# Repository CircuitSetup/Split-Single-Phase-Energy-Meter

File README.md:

# CircuitSetup Split Single Phase Energy Meter

The CircuitSetup ATM90E32 Split Single Phase Energy Meter can monitor the energy usage in your entire home in real time. It can easily be hooked up to an ESP8266 or ESP32 to wirelessly transmit energy usage data into a program like EmonCMS or ESPHome/Home Assistant. It can also be used to monitor solar power generation to keep track of how much power you are making.

#### With the Split Single Phase Energy Meter you can:

*   **Save Money!**
    *   See exactly how much money you're spending on energy in real time
    *   Find appliances that are using too much electricity
    *   Calculate energy usage for a single room to divide an energy bill fairly among roommates
*   **View & Gather Energy Data**
    *   View the energy usage of your entire home
    *   Track solar power generation (two units required)
    *   Calculate how much it costs to charge your electric vehicle
    *   Remote energy monitoring for vacation or rental properties
    *   Review and graph historical energy data
*   **Be Informed!**
    *   Independent of your power utility's meter
    *   Set up alerts for over or under usage
    *   Prevent surprises on energy bills
    *   View usage data in the EmonCMS Android or iOS apps
    *   Automate notifications with your home automation system like "send my phone a message when the dryer is done", or even "if I leave the house, and the oven is on, send me an alert" (programming required)
*   **Spend less on energy monitoring hardware!**
    *   Affordable but very accurate
    *   Save hundreds over popular monitoring systems

The Energy Meter kit available on CrowdSupply:

## Contents

<!-- toc -->
- [Features](#features)
- [Software Setup](#software-setup)
- [Hardware Setup](#hardware-setup)
- [Calibration](#calibration)
- [Troubleshooting](#troubleshooting)
<!-- tocstop -->

## Features:

* **IC: MicroChip ATM90E32**
* **Connectivity**
     * SPI Interface to connect to any Arduino compatible MCU
     * Two IRQ interrupts, and one Warning output
     * Energy pulse output (pulses correspond to four LEDs)
     * Zero crossing output
* **Real Time Data Sampling**
     * Two current channels - up to 200A per channel
     * One voltage channel (expandable to two)
     * Measurement Error: 1%
     * Dynamic Range: 6000:1
     * Gain Selection: Up to 4x
     * Voltage Reference Drift Typical (ppm/°C): 6
     * ADC Resolution (bits): 16
* **Calculates**
     * Active Power
     * Reactive Power
     * Apparent Power
     * Power Factor
     * Frequency
     * Temperature
* **Other Features**
     * Can use more than one at a time to measure as many circuits as you want, including solar power generation
     * Uses standard current transformer clamps to sample current
     * Includes built-in 500mA 3v3 buck converter to power MCU board 
     * Compact size at only 40 mm x 50 mm

## What you'll need:

* Current Transformers for wire:
   * **13mm and less**, the [SCT-013-000 100A/50mA](https://circuitsetup.us/index.php/product/100a-50ma-current-transformer-yhdc-sct-013/) has a 13mm opening for wire.
   * **13.5mm - 16mm - 4/0 AWG** (usually aluminum, 200A service) not thicker than 16mm with insulation, we recommend the [YHDC SCT-016 120A/40mA](https://circuitsetup.us/index.php/product/120a-40ma-current-transformer-yhdc-sct-016-with-3-5mm-jack-16mm-opening/). The ones available on CircuitSetup.us, and included with the energy meter kit have 3.5mm plugs. 

   * **Greater than 16mm**, the [Magnelab SCT-0750-100](https://amzn.to/2IF8xnY) (must sever burden resistor connection on the back of the board since they have a built in burden resistor). These have wire leads and will need an adapter or screw connectors soldered to the energy meter board.

   * Other CTs can also be used as long as they're rated for the amount of power that you are wanting to measure and have a current output no more than 720mA. For safety, they MUST have a built in Zener diode or burden resistor. 
* AC Transformer: [Jameco Reliapro 9v](https://amzn.to/2XcWJjI)
* An [ESP32](https://amzn.to/2pCtTtz), ESP8266, LoRa, or anything else that has an SPI interface.
* Jumper wires with Dupont connectors, or perf board to connect the two boards. The energy meter kit comes with a PCB adapter for an ESP32.
* The software located here to load onto your controller
* [EmonCMS](https://emoncms.org/site/home), ThingSpeak, InfluxDB/Grafana, or similar

## Software Setup

If you purchased an energy meter kit EmonESP is pre-loaded onto the included ESP32. You can skip this section and go to [Setting up EmonCMS](#setting-up-emoncms)

1.  Clone this repository in GitHub desktop or [download all the files and extract them to a folder](https://github.com/CircuitSetup/Split-Single-Phase-Energy-Meter/archive/master.zip)
2.  Place the ATM90E32 folder in your Arduino libraries folder. This is usually under Documents > Arduino > libraries
3.  We highly recommend using [EmonCMS.](https://emoncms.org/site/home) - EmonESP helps to connect and send data directly to EmonCMS
4.  Open **EmonESP > src > src.ino** - you will see several files open, but you'll only need to worry about src.ino
5.  Make sure the **CS_pin** is set to the pin that you are using on your controller board - the defaults are listed in src.ino and in the [hardware section here.](#hardware-setup)
6.  Upload the src.ino to your ESP (If you get any errors at this point, like a missing library, check the [Troubleshooting section on the EmonESP readme.](Software/EmonESP#troubleshooting-upload))
   If you are using an ESP32, [make sure you are using the latest software from the Espressif repository.](https://github.com/espressif/arduino-esp32)
7.  Upload files to the ESP in the data directory via SPIFFS - [see details on how to do this here](https://github.com/CircuitSetup/Split-Single-Phase-Energy-Meter/tree/master/Software/EmonESP#2-install-esp-filesystem-file-uploader)
8.  Follow the directions to configure the Access Point in the [EmonESP directions](/Software/EmonESP#first-setup)

### Setting up EmonCMS 

There are a few options for doing this:
- You can use the [EmonCMS.org service](https://emoncms.org/site/home), which costs roughly $15 a year with the data that we send from the energy meter (you don't _have_ to send all of the data)
- [Install on a computer within your network](https://github.com/emoncms/emoncms). To do this, you will need to have [apache/php/mysql installed](https://www.znetlive.com/blog/how-to-install-apache-php-and-mysql-on-windows-10-machine/)) [This can also be done with a Raspberry Pi.](https://github.com/emoncms/emoncms/blob/master/docs/RaspberryPi/readme.md)
- [Install on a remote web server](https://github.com/emoncms/emoncms). There are some very cheap ways this can be done if you're familiar with setting up web applications.

If you install EmonCMS on a remote web server, or if your home network has a public facing port, this will make it possible to see data on the EmonCMS app ([Android](https://play.google.com/store/apps/details?id=org.emoncms.myapps) or [iOS](https://itunes.apple.com/us/app/emoncms/id1169483587?ls=1&mt=8)) when your phone is outside of your network.

For all but the EmonCMS.org service, (currently for EmonCMS.org these feeds and inputs have to be setup manually) you can automatically setup the energy meter device in EmonCMS:
1. [Install the device plugin](https://github.com/emoncms/device) - this is now included in the default configuration
2. [Upload this file to the Modules > device > data > CircuitSetup folder.](/Software/EmonCMS/circuitsetup_split-phase.json)
3. Once the folder is created and json file is uploaded, go to Setup (top left) > Device Setup > New Device (lower right)
4. Click on CircuitSetup in the left menu
   You will see this: 
   
5. Fill in the Name and Location and click save. 
6. You will then see the fields and inputs - click Initialize:
   
7. You should now see this under Feeds:
   
8. And this under Inputs:

### Other software options
If you would like to use something other than EmonCMS, you can do that too! Make sure the ATM90E32 library is included in the sketch. See the [examples folder](https://github.com/CircuitSetup/Split-Single-Phase-Energy-Meter/tree/master/Software/examples) for examples of how things could be done using JSON or MQTT. Users have already setup feeds to Home Assistant, Influxdb, and Graphina. 

Support for this energy meter, and the ATM90E32 is now included in [ESPHome.](https://esphome.io/components/sensor/atm90e32.html)
[See here for more details](https://github.com/CircuitSetup/Expandable-6-Channel-ESP32-Energy-Meter#esphomehome-assistant) on setting up the meter with ESPHome. [Example configurations are located here.](https://github.com/CircuitSetup/Split-Single-Phase-Energy-Meter/tree/master/Software/examples)

## Hardware Setup
If you purchased an energy meter kit you can skip this section and go to [Installing the Energy Meter](#installing-the-energy-meter)

### Connect your controller to the energy meter
Connect the pins on the Energy Monitor to your MCU. If you have the adapter board, everything should already be connected properly. The following are the default for each, but they can be changed in software if you are using these pins for something else. 

For the ESP32:
*   5 - CS
*   18 - CLK
*   19 - MISO
*   23 - MOSI

For the ESP8266:
*   D8/16 - CS
*   D5/14 - CLK
*   D6/12 - MISO
*   D7/13 - MOSI

Don't forget to hook up the 3V3 and GND pins! 

**The energy meter can supply up to 500mA of 3.3v power to your controller**, so no other external power source should be needed. Some ESP32 dev boards may use more than 500mA when trying to initially connect to WiFi. If this is the case, you may not be able to connect to WiFi. If this happens, we recommend using another power source for the ESP32 - either a 5v DC adapter or a USB phone charger that outputs at least 500mA. It is **not** recommended to leave USB power plugged into an ESP at the same time as the energy meter's power 3V3 output. This can damage components. 

Other pins on your controller can be connected to the WARN and IRQ outputs, but they are not yet implemented in the default software. 

### Using more than one meter
More than one meter can be hooked up to a single MCU to monitor a solar grid, for example. 

To do this:
- Connect all CLK, MISO, and MOSI pins together
- Connect the GND and 3V3 from one meter to the MCU
- Connect the CS pin of one energy meter to an open GPIO on your MCU, and the CS pin on the second energy meter to another open GPIO on your MCU. These pins must be set in the software. See the [examples folder](/Software/examples) for the example with more than one energy meter.
- If you would like to monitor voltage from two sources, you will need two AC transformers. If only one voltage, you can split the output of 1 AC transformer using a 2.5mm DC jack Y-cable.

You can also [purchase a solar adapter here](https://circuitsetup.us/index.php/product/energy-meter-solar-esp32-adapter-2x-split-phase-meter-headers-space-for-spi-oled-screen/).

## Installing the Energy Meter
### Warning
To install the current transformers to measure current, your breaker panel must be opened to clamp them around your mains wires.
**High voltage AC power is VERY dangerous! If you are not comfortable working around AC voltage, we strongly encourage you to hire a qualified electrician.**

### **Disclaimer**
**The Split-Single Phase Energy Meter should be installed by a qualified professional, and in compliance with all local electrical codes that apply. CircuitSetup, and its parent company Sugarman Studios, LLC, cannot be held liable for damages or injury incurred by incorrectly installing the Split-Single Phase Energy Meter.**

The Split Single Phase Kit:

1. Decide where to mount the energy meter. We recommend installing the box outside of your panel for a better WiFi signal.  **The current transformer wires will need to be passed through a grommet in the side of the panel** It is against NEC code (US) to not route wires going in or out of an electrical panel through a grommet. 
2. The AC Transformer should be plugged into an outlet close to the panel. If you do not have one close, it is recommended that you have one installed by a licensed electrician. It isn't absolutely necessarty that the outlet is close to the panel, but it will give you more accurate readings. 

### Plug in the AC Transformer
Take note of the side of the split phase that the breaker for the AC transformer is on. This is important for connecting the CTs in the correct direction (see below section)
3. **If you wish to read the voltage from both sides of your panel** :
   - Hook up a second AC transformer to a single pole breaker, or a second outlet, that is wired to the opposite phase of the first AC transformer. If the breaker for the first outlet is on the left of your panel, you will need to wire the second AC transformer or outlet to a breaker on the right of the panel (single split phase breaker panels)
   - Sever jumper JP3 on the back of the energy meter **before hooking up the second AC transformer.** 
   - Solder 2 pin headers, or a female pigtail that matches your second AC transformer plug, to the left of the main AC power plug labeled GND and VC+. 
   - Hook up the second AC transformer to the “GND” (neutral) and “VC+” pins. **You want the wire that is intended to be neutral for the AC transformer to go on the GND terminal of the meter**. This wire usually has a white stripe on it. If the wires are swapped the 2 AC transformers will be in phase, and your current readings will output as negative.

### Connect Current Transformers to the energy meter
Before connecting the current transformers around your mains wires, plug them into the energy meter.

If your current transformers (CTs) have 3.5mm phono connectors, you hopefully have the version of the Energy Meter with these connections (v1.3+ has footprints for both). If you have the screw connectors, the phono connectors will have to be cut off. There should only be two wires regardless. For the screw connector version, be careful to connect the positive to the correct terminal. If these are reversed, things will not be damaged, but the reading will read negative.

If your current transformers have a built-in burden resistor, sever the jumpers on the back of the board to disable the 12ohm burden resistors. Alternatively, if you are reading smaller loads and would like more accurate readings, you can insert your own higher value burden resister across the positive and negative screw terminals.

If you purchased an energy meter kit with the black SCT016 current transformers, or have the blue SCT-013-000, these do not have a built-in burden resistor, but have a TVS diode instead. 

### Connect Current Transformers to your mains
1. Note the direction of the arrows on the top of the current transformers. 
   - If you are measuring 1 voltage (the default configuration): 
      1. CT1 should be on the same side of the split phase as the breaker for the plug that the AC transformer is plugged into, and should point in the direction of the current flowing into your house.
      2. CT2 should point in the opposite direction as CT1. Note: If you are measuring a second voltage with the VC+ input this CT will go in the same direction as the first.
2. Clip the current transformers around the two large main wires, usually at the top of the breaker box. **DO NOT TOUCH BARE METAL ON THESE WIRES**. There is one current transformer for each phase. 
3. Make sure the current transformers are not in the way of anything else, and are snapped closed around the wires. **Do not force them shut – if they will not close you will need a larger current transformer**

### Solar Kit Setup ###
The solar kit comes with 2 meters, 4 current transformers, and optionally, 2 AC transformers.

#### AC Transformers
**The 1st AC transformer**, L1, should be plugged into an outlet the same way as noted above in the "Plug in the AC Transformer" section

**The 2nd AC transformer**, L2, for the solar kit should be plugged into an outlet that is on the opposite phase than the first AC transformer. If you do not have an outlet, we recommend having a licensed electrician install one.

It is possible to power both energy meters with one AC transformer, you will just need a Y splitter. Close attention needs to be paid to the direction of the current transformers to properly measure the direction current is flowing.

#### Current Transformers
The mains current transformers (CT1, CT2) should be connected the same way as noted above starting with section "Connect Current Transformers to the energy meter"

Current transformers to measure solar energy generation (SCT1, SCT2) should be connected to the wires coming into your panel from your solar inverter. This is usually a dual pole breaker with 2 hot wires (in the US). The arrows on the CTs should be opposite eachother, like with the mains CTs. The wire that is connected to the side of the panel that is the same as the solar AC transformer will point towards the panel. It may take some trial an error to get this correct. 

Energy generated by solar, but not used by your house will register on the mains CTs as negative, since energy is flowing back to the grid. In EmonCMS this calculation is done automatically assuming you have set up the "Solar Kit" device.

## Calibration

If you purchased a kit that came with current transformers **and** an AC Transformer, you should not have to calibrate anything unless you want to. If you are providing your own AC Transformer, you will need to calibrate the voltage.

The default configuration of the Energy Meter software is set to use the SCT-016 120A/40mA current transformers, and the [Jameco Reliapro 9v AC transformer](https://amzn.to/2XcWJjI). There are also values for 100A Magnalab, SCT-013 100A 50mV current transformers, and the 12v version of the AC transformer located in the **energy_meter.h** file, and in the EmonESP web interface. Simply change the values under CALIBRATION SETTINGS if you are using a 12v AC Transformer or the Magnalab current transformers.  **If you are using any of these you likely will not need to calibrate, but if you want to be sure your readings are the most accurate then calibration is recommended.** 

Alternatively, if you have equipment that can read active and reactive energy pulse outputs, CT1-CT4 pins can be used for this. It is recommended that these connections are opto-isolated to prevent interference. 

### For calibration you will need:
1.  A multi-meter, or to make it easier and safer, a [kill-a-watt](https://amzn.to/2TXT7jx) or similar. A clamp meter will also work if you would like to measure mains power directly.
2.  A hair dryer, soldering iron, electric heater, or anything else that uses a large amount of resistive current.
3.  A modified power cable that allows you to put a current transformer around only the hot (usually black) wire.

### Setup
1.  At this point all wires should be connected between your ESP and the Energy Monitor.
2.  Connect the Energy Monitor to the AC Transformer and plug it in - the ESP and Energy Meter should both have power. If either do not, check your connections.

#### With the Arduino IDE
1.  Open the Arduino IDE
2.  Connect your ESP to your computer via USB cable
3.  Select the COM port under Tools > Port
4.  Go to Tools > Serial Monitor
5.  Values should be scrolling by. If you do not see anything in the serial window, make sure the correct COM port is selected for your ESP in the Arduino IDE.

#### With EmonESP
1.  The first time the ESP32 or ESP8266 is started with EmonESP, it will not be connected to a local router, and will go into SoftAP mode. You can connect to the interface via a cell phone or other wireless device to access the interface via a web browser at 192.168.4.1 or emonesp.local. For more details on this see [EmonESP WiFi Connection](/Software/EmonESP#1-wifi-connection)
2.  If the ESP is already connected to a network, you can access the interface with the IP address that your router assigned to it.
3.  Go to the Calibration section:

### Voltage Procedure 

1.  In the Serial Monitor window or in EmonESP under 4. Latest Data, view the value for Voltage - take note of this (if you are getting a value above 65k, something is not hooked up or working correctly)
2.  Take a reading of the actual voltage from an outlet in your house.  For the Kill-a-watt, just plug it in, and select voltage. Compare the values.
3.  Adjust the value for VoltageGain in energy_meter.h or EmonESP by calculating:

<pre>New VoltageGain = (your voltage reading / energy monitor voltage reading) * VOLTAGE_GAIN</pre>

VOLTAGE_GAIN is the value currently set for the voltage gain parameter in energy_meter.h.

Test again after adjusting the value and re-uploading the sketch to your ESP. If it is still off, do the procedure again, but replace VOLTAGE_GAIN with the last value used. 

If you are not located in the US and have 50hz power, change the Frequency value to 389

### Current Procedure
For calibrating **CurrentGainCT1 & CurrentGainCT2**:

1.  In the Serial Monitor window or in EmonESP under 4. Latest Data, view the value for Current 
2.  If the value is negative, you are either exporting power (solar), or the current transformer is backwards.
3.  Compare what you are seeing for current from the Energy Monitor to the reading on the Kill-a-watt
4.  Adjust the value for CurrentGainCT1 or CurrentGainCT2 in energy_meter.h or EmonESP by calculating:

<pre>New CurrentGainCT1 or CurrentGainCT2 = (your current reading / energy monitor current reading) * CURRENT_GAIN_CT#</pre>

CURRENT_GAIN_CT# is the value currently set for the current gain parameter in energy_meter.h.

Test again after adjusting the value and re-uploading the sketch to your ESP. If it is still off, do this again, but replace the CURRENT_GAIN_CT# with the last value used. It is possible that the two identical current sensors will have different CurrentGain numbers due to variances in manufacturing, but it shouldn't be drastic. Note that the positioning of the CT sensor on the hot wire can influence the current reading. 

For more details, see the Calibration Procedure in the [Microchip Application notes.](http://ww1.microchip.com/downloads/en/AppNotes/Atmel-46103-SE-M90E32AS-ApplicationNote.pdf)

## Troubleshooting
### I'm not getting any data from the energy meter
If you have an energy meter kit:
- **Check that the ESP32 is seated properly.** Take it all the way out, then back in again to make sure. It should click into place. If you find you're only getting a signal when holding down the ESP32, you can try removing the black plastic around the base of the pins of the esp32, to push it down further. This is best accomplished with flush cutters. If you rather not do that, please contact us.
- If you're getting all 0 readings from the meter, try the steps above. If that does not work, please contact us.

If you do not have a kit:
- If you are getting all 65535 readings from the meter, then the connection from the ESP32 to the meter is not correct. Please check your wires.

### I'm getting a very low power factor reading, and wattage seems off
One of your CT clamps is probably backwards - flip it around. If they are both oriented in the same direction, this will not happen. 

### The ESP32 doesn't stay connected to WiFi
Make sure that the ESP32 has a good WiFi signal. The RSSI (viewable in the EmonESP web interface) should be, at the least, -70db.

For the CircuitSetup version of EmonESP:
- If the ESP32 loses the connection to the configured access point it will try 3 times over a 30 second period to reconnect. 
- If it cannot reconnect, it will go into SoftAP mode and broadcast a signal so it can be reconfigured via the web interface, if necessary. 
- If nothing happens after 5 minutes, it will try to reconnect to the configured access point again. 

### The ESP32 with CitcuitSetup EmonESP freezes and the blue LED does not blink
See the steps above for staying connected to WiFi. If that does not work, try one of the following:
1. Load [the latest firmware via the EmonESP web interface](https://github.com/CircuitSetup/Split-Single-Phase-Energy-Meter/releases). 
   - Download the latest .bin file from the link above
   - Open http://EmonESP_IP/upload (6. Firmware)
   - Click "Choose File", select the .bin file, then "Update Firmware"
   - The file will upload to the ESP32, and it will reset
   - After about 20 seconds the upload page will reload - you can return to the main page to verify everything is working properly
   
2. Close the browser window open to the EmonESP interface. There was a bug, that has since been corrected in v2.5.3, that would cause the ESP32 to freeze if a browser window was left open. It may also not close a browser session, which caused a memory leak, and eventual freeze.
3. Use an AC Transformer with a higher current output, like the [Jameco 112336](https://www.jameco.com/z/ADU090150A2231-AC-to-AC-Wall-Adapter-Transformer-9-Volt-1500mA-Black-Straight-2-5mm-Female-Plug_112336.html). The voltage calibration procedure will need to be done.
4. If the power being read is especially noisy, the energy meter IC and on-board low pass filters are pretty good at filtering, but sometimes this can cause the ESP32 to freeze. To remedy, bypass the on-board power supply:
   - If you have a hot air soldering gun:
      1. Remove the rectifier diode next to the power jack
      2. Use a USB style AC/DC adapter or phone charger to power the ESP32 via the micro-USB jack
      3. Use the AC transformer as you did previously
   - If you only have a regular soldering iron:
      1. Only the voltage 2 channel will be used in this method, so a modification to account for this in software will have to be done
      2. Solder a header on to "VC+" and "GND" next to the power jack
      3. Sever the JP3 connection on the back of the board
      4. Crimp or solder on a header that matches the one soldered onto the board in step 1 - **be careful to not reverse the polarity!**
      5. Use a USB style AC/DC adapter or phone charger to power the ESP32 via the micro-USB jack
      
### How do I change the network AP the ESP32 is connected to with EmonESP? 
1. Turn off the router that the ESP32 is configured on, and the meter/ESP32
2. Turn on the meter/ESP32
3. The ESP32 will go into soft AP mode after 30 seconds of not being able to connect to the configured AP. You can confirm this by checking the blue led. It will blink once every 2 seconds.
4. Connect to the ESP32 like you did when you first configured EmonESP. From there you can set it to connect to the new network AP.

### How do I reset the login/password to the EmonESP admin page?
To do this you'll have to reset EmonESP to default. This will erase any saved settings, like wifi configuration and connections.

1. Remove the ESP32 off of the pcb
2. Power the ESP32 via USB (If you want, open a serial window to see what it's outputting)
3. Connect Gnd (upper left) with GPIO3 (5th pin from upper left) with a jumper wire
4. Wait 15 seconds (10 minimum, but 15 to be sure). If you have a serial window open, it'll say "factory reset"
## Licenses
Hardware license: CERN v 1.2

Documentation license: CC BY 4.0

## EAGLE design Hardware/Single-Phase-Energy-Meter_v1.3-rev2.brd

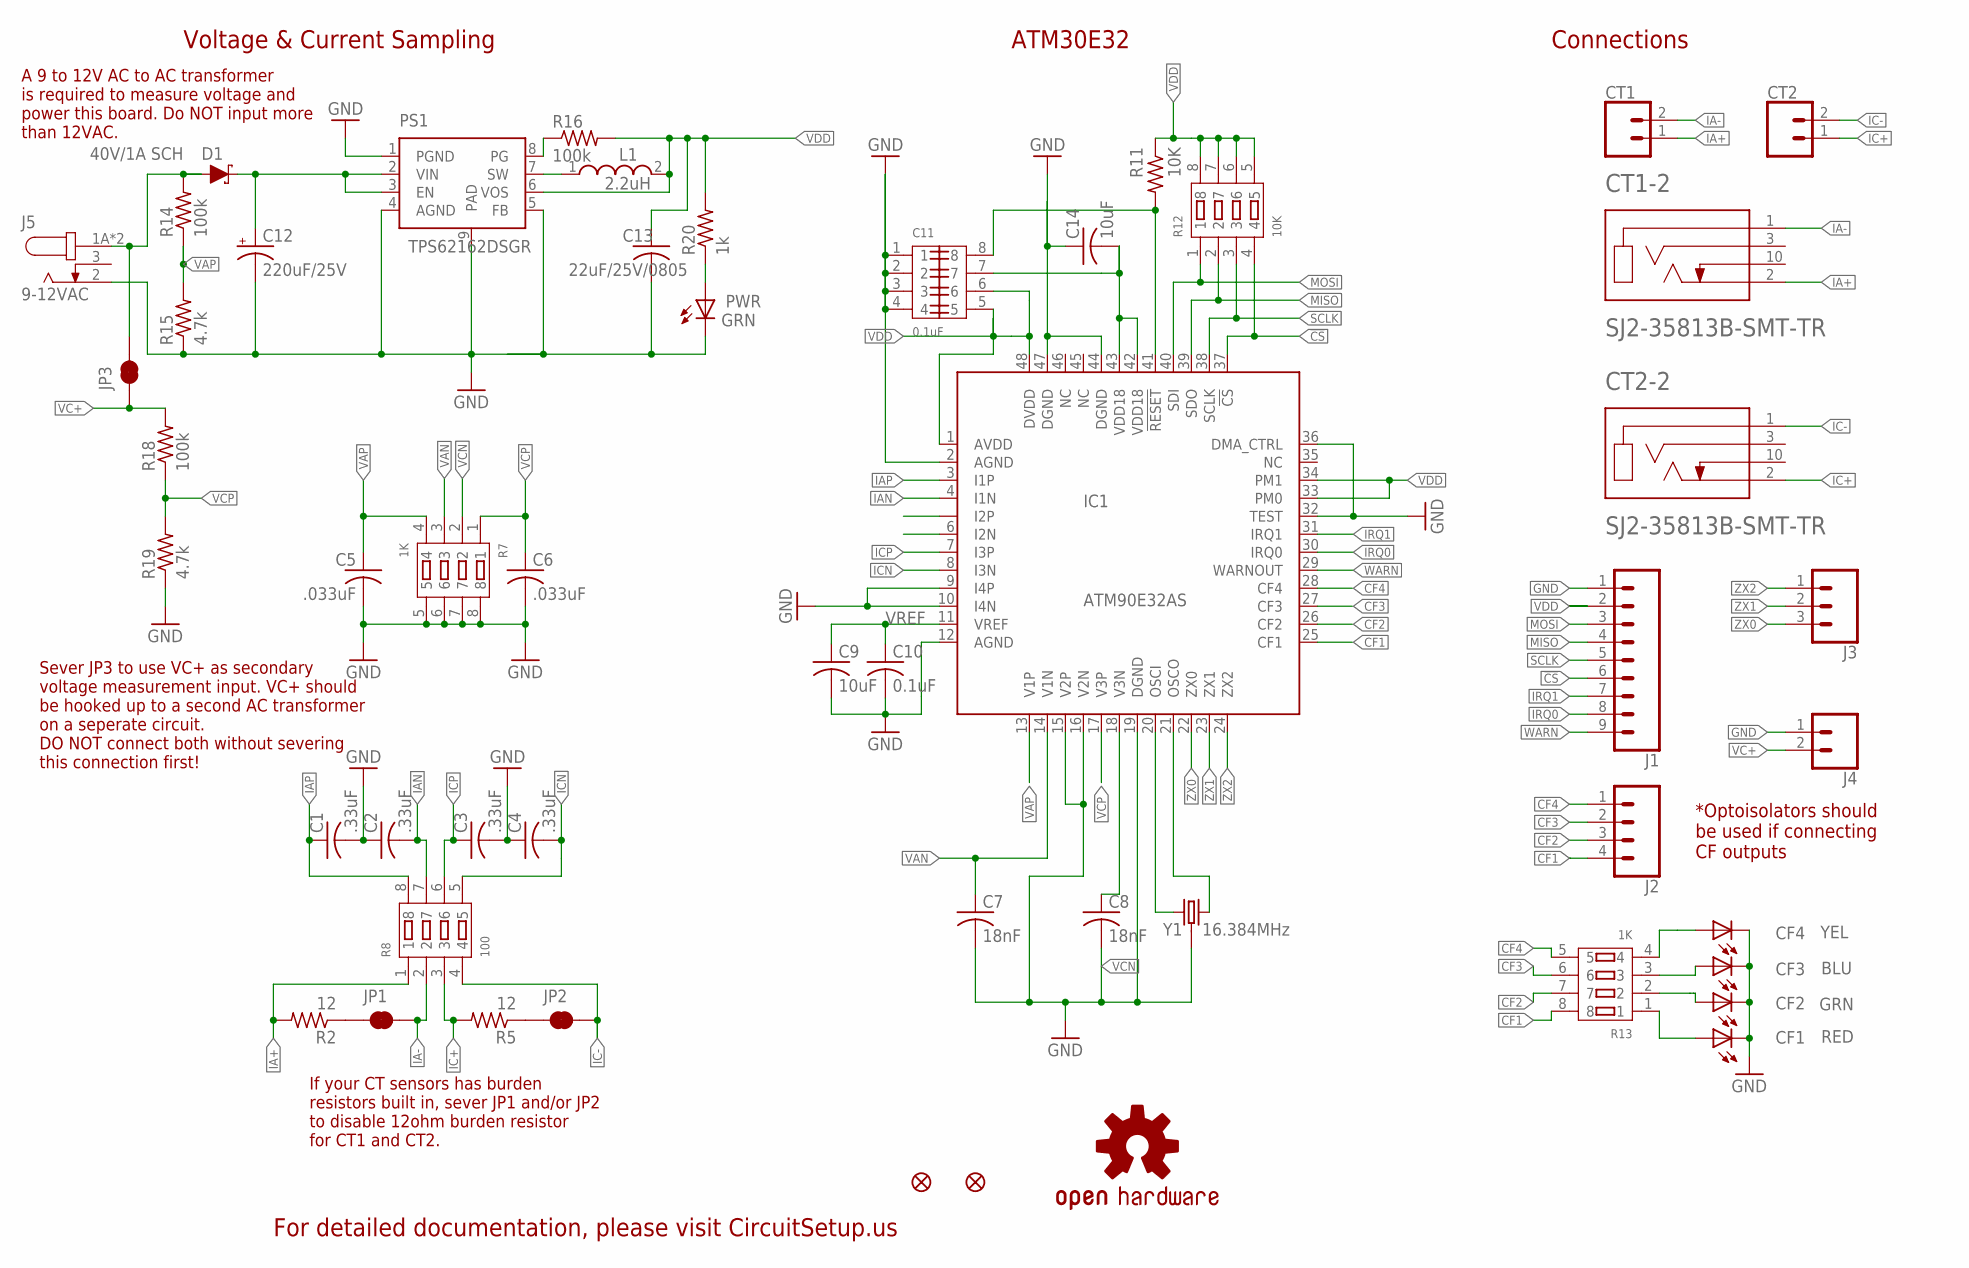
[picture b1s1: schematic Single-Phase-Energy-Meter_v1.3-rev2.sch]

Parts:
C1, C2, C3, C4: .33uF; C0603
C5, C6: .033uF; C0603
C7, C8: 18nF; C0603
C9, C14: 10uF; C0603
C10: 0.1uF; C0603
C11: 0.1uF; CAPCAF80P320X160X70-8
C12: 220uF/25V; 153CLV-0605
C13: 22uF/25V/0805; C0805
CF1: RED; CHIP-LED0603
CF2: GRN; CHIP-LED0603
CF3: BLU; CHIP-LED0603
CF4: YEL; CHIP-LED0603
CT1, CT2: CONN_023.5MM; SCREWTERMINAL-3.5MM-2
CT1-2, CT2-2: SJ2-35813B-SMT-TR; CUI_SJ2-35813B-SMT-TR
D1: 40V/1A SCH; SMA-DIODE
FD1, FD2: FIDUCIALUFIDUCIAL; FIDUCIAL-MICRO
IC1: ATM90E32AS; QFP50P900X900X120-48N
J1: CONN_09; 1X09
J2: CONN_04; 1X04
J3: CONN_03; 1X03
J4: CONN_02; 1X02
J5: 9-12VAC; CUI_PJ-002AH-SMT-TR
JP1, JP2, JP3: JUMPER-SMT_2_NC_TRACE_SILK; SMT-JUMPER_2_NC_TRACE_SILK
L1: 2.2uH; INDPM4042X200N
LOGO1: OSHW-LOGOS; OSHW-LOGO-S
PS1: TPS62162DSGR; SON50P200X200X80-9N
PWR: GRN; CHIP-LED0603
R2, R5: 12; R0603
R7, R13: 1K; RA1206-8
R8: 100; RA1206-8
R11: 10K; R0603
R12: 10K; RA1206-8
R14, R16, R18: 100k; R0603
R15, R19: 4.7k; R0603
R20: 1k; R0603
Y1: 16.384MHz; CRYSTAL-SMD-3.2X2.5MM

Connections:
!CS: IC1.37 (!CS), J1.6, R12.4
!RESET: C11.8, IC1.41 (!RESET), R11.2
CF1: IC1.25 (CF1), J2.4, R13.8
CF2: IC1.26 (CF2), J2.3, R13.7
CF3: IC1.27 (CF3), J2.2, R13.6
CF4: IC1.28 (CF4), J2.1, R13.5
GND: C1.2, C2.1, C3.2, C4.1, C5.2, C6.2, C7.2, C8.2, C9.2, C10.2, C11.1, C11.2, C11.3, C11.4, C12.-, C13.2, C14.1, CF1.C, CF2.C, CF3.C, CF4.C, IC1.2 (AGND), IC1.9 (I4P), IC1.10 (I4N), IC1.12 (AGND), IC1.15 (V2P), IC1.16 (V2N), IC1.19 (DGND), IC1.32 (TEST), IC1.36 (DMA_CTRL), IC1.44 (DGND), IC1.47 (DGND), J1.1, J4.1, J5.2, PS1.1 (PGND), PS1.4 (AGND), PS1.5 (FB), PS1.9 (PAD), PWR.C, R7.5, R7.6, R7.7, R7.8, R15.1, R19.1, Y1.2 (3), Y1.4 (3)
IA+: CT1.1, CT1-2.2 (TIP), R2.2, R8.1
IA-: CT1.2, CT1-2.1 (SLEEVE), JP1.2, R8.2
IAN: C2.2, IC1.4 (I1N), R8.7
IAP: C1.1, IC1.3 (I1P), R8.8
IC+: CT2.1, CT2-2.2 (TIP), R5.2, R8.3
IC-: CT2.2, CT2-2.1 (SLEEVE), JP2.2, R8.4
ICN: C4.2, IC1.8 (I3N), R8.5
ICP: C3.1, IC1.7 (I3P), R8.6
IRQ0: IC1.30 (IRQ0), J1.8
IRQ1: IC1.31 (IRQ1), J1.7
MISO: IC1.39 (SDO), J1.4, R12.2
MOSI: IC1.40 (SDI), J1.3, R12.1
unnamed: JP1.1, R2.1
unnamed: JP2.1, R5.1
unnamed: CF4.A, R13.4
unnamed: CF3.A, R13.3
unnamed: CF2.A, R13.2
unnamed: CF1.A, R13.1
unnamed: L1.1, PS1.7 (SW)
unnamed: PS1.8 (PG), R16.1
unnamed: PWR.A, R20.1
OSCI: IC1.20 (OSCI), Y1.1
OSCO: IC1.21 (OSCO), Y1.3 (2)
SCLK: IC1.38 (SCLK), J1.5, R12.3
VA+: D1.A, J5.1A (1), J5.1B (1), JP3.2, R14.2
VAN: C7.1, IC1.14 (V1N), R7.3
VAP: C5.1, IC1.13 (V1P), R7.4, R14.1, R15.2
VC+: J4.2, JP3.1, R18.2
VCN: C8.1, IC1.18 (V3N), R7.2
VCP: C6.1, IC1.17 (V3P), R7.1, R18.1, R19.2
VDD: C11.5, C11.6, C13.1, IC1.1 (AVDD), IC1.33 (PM0), IC1.34 (PM1), IC1.48 (DVDD), J1.2, L1.2, PS1.6 (VOS), R11.1, R12.5, R12.6, R12.7, R12.8, R16.2, R20.2
VDD18: C11.7, C14.2, IC1.42 (VDD18), IC1.43 (VDD18)
VIN1: C12.+, D1.C, PS1.2 (VIN), PS1.3 (EN)
VREF: C9.1, C10.1, IC1.11 (VREF)
WARN: IC1.29 (WARNOUT), J1.9
ZX0: IC1.22 (ZX0), J3.3
ZX1: IC1.23 (ZX1), J3.2
ZX2: IC1.24 (ZX2), J3.1

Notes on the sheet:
ATM30E32
Voltage & Current Sampling
Connections
*Optoisolators should be used if connecting CF outputs
If your CT sensors has burden resistors built in, sever JP1 and/or JP2 to disable 12ohm burden resistor for CT1 and CT2.
Sever JP3 to use VC+ as secondary voltage measurement input. VC+ should be hooked up to a second AC transformer on a seperate circuit. DO NOT connect both without severing this connection first!
A 9 to 12V AC to AC transformer is required to measure voltage and power this board. Do NOT input more than 12VAC.
For detailed documentation, please visit CircuitSetup.us

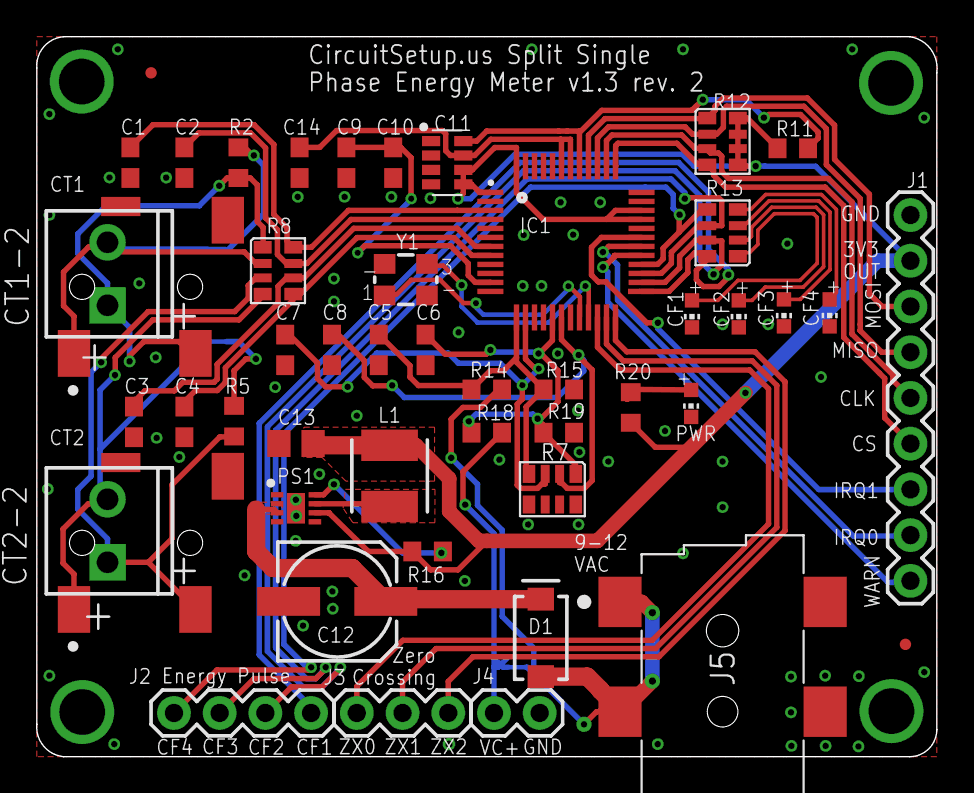
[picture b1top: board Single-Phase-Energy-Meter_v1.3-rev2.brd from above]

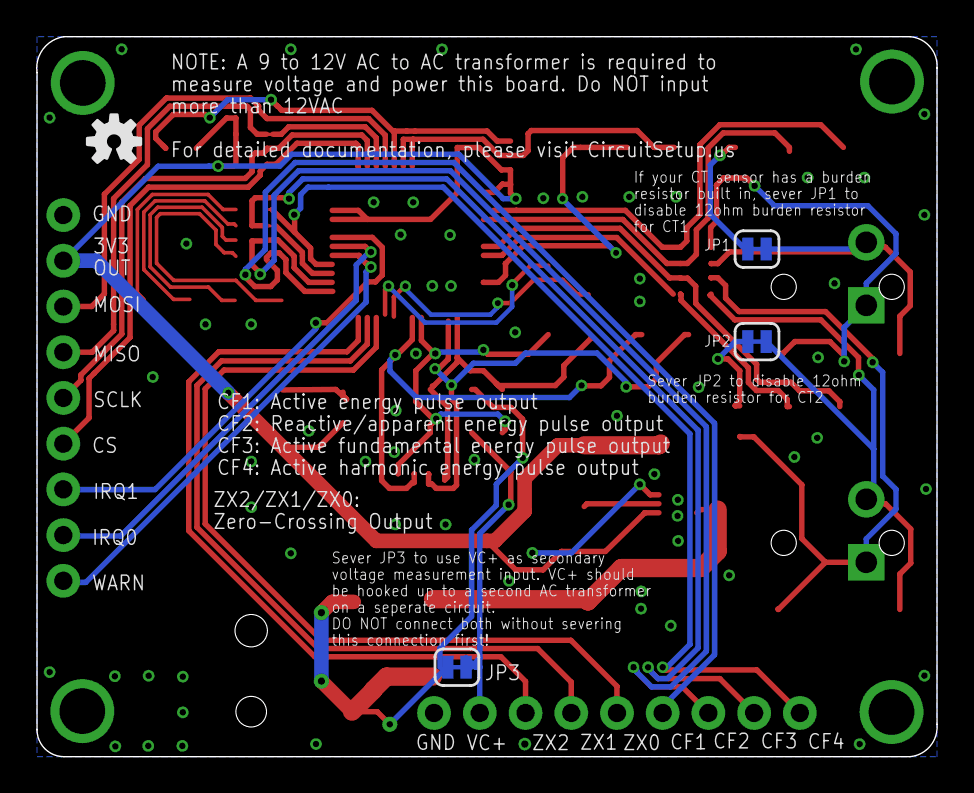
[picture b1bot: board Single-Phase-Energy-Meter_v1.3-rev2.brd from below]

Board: 2 copper layers, 50.0 x 40.0 mm, 52 parts (4 on the bottom side), 45 nets.

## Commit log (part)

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2019-05-06 added files
2019-05-06 images
2019-05-07 added schematic and data sheets
2019-05-09 Create ATM90E32_MQTT.ino
    add MQTT example
2019-05-11 updated feed and input setup for EmonCMS
2019-05-14 Updated the ATM90E32 library significantly
    - Replaced lineGain with much more useful PGAGain, which increases the gain on current channels. Useful if using smaller CTs (1x) or larger CTs, like 200A (4x). The default is 2x
    - Added config variable for line frequency. This allows the frequency setting to be switched in the front end software. Default is 60hz.
    - Fixed GetActivePower, GetApparentPower, GetPowerFactor - all of these were not taking into account the lower 16 bit register, and were not outputting the correct numbers
    - Fixed GetPowerFactor - the registers for power factor sometimes goes out of bounds for unknown reasons. Corrected this by doing a check on the output, and outputting 0
2019-05-14 Added changes to EmonCMS & example based on changes in ATM90E32 library
2019-05-14 update to work with new library variables
2019-05-14 added wire diameter chart
2019-05-15 changed license to MIT
2019-05-23 open source licenses
2019-05-24 v1.4 meter layout & solar adapter pcb
    Tweaks in v1.4:
    - changed to higher output TI SMPS
    - added C16 & C17 caps to help with filtering
    - moved bypass caps closer to the IC
    Solar adapter:
    - allows 2 energy meters to be used
2019-05-24 Update LICENSE
2019-05-24 Update src.ino
    added extra parameter to ATM90E32 initialize to accomodate for 6 channel meter
2019-05-24 accomodate for 6 channel meter
2019-05-25 updated to work with latest library revision
2019-05-25 Organized the energy meter specific code
    * Split out the energy_meter specific code into its own module
    * Added flag to enable or disable the energy_meter specific code
    * Added detection for Net Energy +/-
    * Fixed "Latest Data" pane on web UI
2019-05-27 set default values
2019-05-30 fixed on board LED variable
2019-05-30 solar software for EmonCMS
2019-06-03 fixed totalWatts calcu & added default calibration val for SCT-016 CTs
2019-06-04 Home Assistant example with MQTT
2019-06-11 added details and libraries
2019-06-12 binaries for esp32
2019-06-12 cleaned up a little & added new default voltage calibrations
2019-06-14 updated v1.4 of pcb
    Changes from v1.3:
    - Changed SMPS from TI TPS62162 to TPS32142, which can output more power. This will help with power hungry MCU's
    - Added 10uf cap, C15 before SMPS
    - Added C17 as part of SMPS requirement
    - Added 10uf cap C16 for additional noise filtering on IC1 DGND pin
    - Moved filtering caps closer to IC1
2019-06-14 solar box files
2019-06-14 fixed default view, 3d packages & removed unused layers
2019-06-14 Update circuitsetup_split-phase.json
    removed redundant active power
2019-06-17 Updated offset register values & other improvements
    - Tuned offset register values which will make metering values more accurate
    - Calibrated phase angle for more accurate small current values
    - Removed calculation that would not allow some metering values to ever be negative
    - Added switch to allow or not allow for negative values (default is no negative values)
    - Accomodated for case where one active power reading would be negative because it would be out of phase with the other with only 1 voltage reading.
    - Removed redundant front end total watts calculation
2019-06-18 updated for 9v AC Jameco 157041
    ... this model will come with the kits
2019-06-28 Added ability to set calibration values in web interface
    - Added calibration values to web interface
    - Fixed firmware upload via web interface (and made messages more descriptive)
    - added SPIFFS detection in firmware upload so this bin is uploaded to correct part of memory
    - changed dependency on OTA library (now Update.h) for ESP32 - the one being used was depricated
    - set hostname correctly for ESP32
    - captive portal redirect disable when not in AP mode (otherwise this spews a bunch of wifiudp.h errors)
2019-06-28 Moved calibration parameters from constructor to ::begin
    - calibration parameters were moved from constructor to begin so values can be gathered from web interface if present. This can't be done before the main function otherwise.
    - Added destructor
2019-06-28 removed variables from constructor
2019-06-28 updated examples according to changes in library
2019-07-03 Lots of updates to how wifi functions
    -Redid how wifi reconnects if client connection is lost, changs to AP mode, then retries to connect again
    - Added ability to go into AP mode or reset everything by holding down an assigned button
2019-07-09 added solar values to web interface
2019-07-16 Updated behavior of ESP led
    - Added LED on time so it's more of a flash
    - Added STA_CONNECTED_TIME for time interval when connected to wifi.
    - if AP mode & disconnected - blink every 2 seconds
    - if AP mode & someone is connected - blink fast
    - if Client mode - slow blink every 4 seconds
2019-07-16 Updated header txt
2019-07-19 Fixed DNS captive portal when ESP is in AP mode
    - compiled bin with latest ESP32 IDF
    - disabled OTA for esp32, not really needed anyway since the web interface can update firmware
2019-07-25 Added error checking to admin and calibration fields
2019-07-26 Hidden password and API fields
    - Password and API fields are now now password form fields. If they are populated a dummy password is returned on the EmonESP GUI
    - Added option to prevent ESP from going into SoftAP mode if connection to main wifi is lost. ESP will continue to try to reconnect to main wifi if configured.
    - Increased default interval for trying to reconnect to wifi directly after losing connection to 10 seconds 3 times - from SoftAP mode to 5 min.
    - Added variable in wifi.h WIFI_CLIENT_DISCONNECT_RETRY (set for 10 seconds)
2019-08-01 Added no AP firmware...
    Normally when the connection to the main wifi AP is lost, the software goes into AP mode so it can be reconfigured if needed. This is turned off, and will keep trying to reconnect to the wifi AP that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
    For this version the only way to change the AP is to ground GPIO 3 for 5 seconds to put the ESP32 into AP mode.
2019-08-16 New renderings
2019-08-16 Update emonesp_v2.5_noAP_lost_conn.bin
    compiled with tweaked esp-idf wifi settings
2019-08-25 Compiled with latest esp32-arduino 1.0.3 rc2
    - Cleaned up spacing and formatting
    - Set WiFi.disconnect to not disable esp32 wifi when called
2019-08-27 Fix for reading 240v properly
2019-08-29 Update README.md
    added ESPHome setup, and example configs link
2019-08-29 Update readme.md
    added Arduino suggested options pic for ESP32
2019-09-06 Create HA-ESPHome_energy_meter.yaml
    -example config file for Home Assistant with ESP32 running ESPHome
2019-09-11 Updated solar EmonESP to match regular build
    - added addition calibration fields for solar in web interface
2019-09-11 pics of assembled pcbs and kits
2019-09-18 Update README.md
    - added troubleshooting steps
    - proofed everything
    - formatting
2019-09-25 include ATM90
2019-09-25 added esp32
2019-09-27 v2.5.3 - Fixed crashing
    - Firmware files Compiled with Arduino core 1.0.3
    - fixed crashing when browser is left open
    - fixed memory leak when a browser session isn't closed properly, which would result in a crash (updated AsyncTCP, and ESPAsyncWebServer)
    - disabled captive portal, which was causing crashes related to heap, and sessions in the SoftAP
    - moved some includes to .h files for better consistency
2019-09-27 SPIFFS.h included only for ESP32
2019-10-03 Update circuitsetup_split-phase.json
    cleaned up formatting
    added frequency
2019-10-03 corrected file extension
2019-10-08 added hash arduino library
2019-10-09 Update web_server.h
    moved hash.h to compile with esp8266 only
2019-10-09 Update README.md
    made solar install more clear
2019-10-11 updated images
2019-10-14 Update README.md
    added instructions for connecting to a new AP
2019-10-28 removed hash library - not needed
2019-10-28 added hardware pics
2019-10-29 mqtt & influxdb images
2019-11-08 Fixed total current calculation for solar
2019-11-08 allow mqtt field to be blank again once filled in
2019-11-08 compiled with Arduino core v1.0.4
2019-11-21 added spiffs.bin
2019-11-21 Fixed power factor & other small tweaks
    - Fixed power factor calculation
    - added SagPeakDetCfg, Sag and Voltage peak detect period and set to 20ms
    - adjusted power startup valuesto be more consistent
    - removed calibrationError since there is no checksum on the 32 (there is on the 36)
    - register numbers in comments
    - Corrected F register names - these are different on the 32 and are voltage & current peaks. On the 36 they are THD, which the 36 doesn't have.
2019-12-03 add comment for voltage calibration
    v1.4 purchased after 11/1/2019 and rev.3 use a different voltage divider and will have a lower calibration value for voltage - for example 7611 - 9v AC Transformer - Jameco 157041
2019-12-03 Update ATM90E32_Basic_SPI.ino
    * For Meters > v1.4 purchased after 11/1/2019 and rev.3
    * 7611 - 9v AC Transformer - Jameco 157041
2019-12-03 Update Home_Assistant_MQTT.ino
    * For Meters > v1.4 purchased after 11/1/2019 and rev.3
    * 7611 - 9v AC Transformer - Jameco 157041
2019-12-03 Update sensor.yaml
    removed redundant total watts
2019-12-03 v2.5.5 - fixes power factor calculation
    - ATM90E32 library fixed to calculate power factor correctly.
    - Upped version to v2.5.5
    - removed canBeNegative for regular meter so its easy to tell when a current transformer is backwards. If one is backwards, real power calculations will be off because power factor will be off.
2019-12-08 Update README.md
    Added reset to default info
2020-01-10 Update README.md
    added links
2020-01-16 Update README.md
    Changed Gaphina to Grafana
2020-02-06 fix for not connecting to anon hass.io MQTT broker
2020-02-26 added note for measuring current over 65A
2020-02-26 added calibrations for different CTs
2020-03-09 Update README.md
    added MySQL to Home Assistant
2020-05-19 Replaced MQTT lib with async, watchdog enabled, WifiClient
    - MQTT now uses async-mqtt-client to prevent MQTT from blocking
    - The esp32 watchdog is now enabled
    - A lot of String variables changed to char
    - HTTPClient changed to properly use WifiClient lib
2020-07-02 Update README.md
    added better instructions for adding a second voltage measurement
2020-08-25 Update readme.md
    updated memory locations for esptool.py
2020-10-04 fix config form to accept '0' to disable PGA
2021-05-04 Update circuitsetup-6_channel_solar.json
    fix use calculation - change import to house_import under Total Solar Power
2021-05-04 Update circuitsetup-6_channel_solar.json
    removed extra voltage input
    added power factor inputs/feeds
2021-05-04 Update circuitsetup-6_channel_solar.json
    use calculation correction (again)
2022-02-04 Update HA-ESPHome_energy_meter_detailed_power.yaml
    added device_class: energy, state_class: total_increasing to properly work in the latest Home Assistant
2022-06-23 Fix compile errors, add ability to disable WiFi/MQTT for calibration, add auto-reboot on number of failures so sensor auto-reconnects after server reboot, update sensor.yaml example to play nicely wi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
2022-06-23 Add in a current multiplier feature for 200A clamps that need to use 1X gain and would like larger range. Adjust total wattage returned to be apparent power instead of real power as this is what most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
2022-08-18 Update README.md
    updated ESPHome links
2022-10-21 Update Home_Assistant_MQTT.ino
    updated PGA gain notes

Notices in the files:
parts and their libraries:
SparkFun-Connectors: Licensing: Creative Commons ShareAlike 4.0 International - https://creativecommons.org/licenses/by-sa/4.0
